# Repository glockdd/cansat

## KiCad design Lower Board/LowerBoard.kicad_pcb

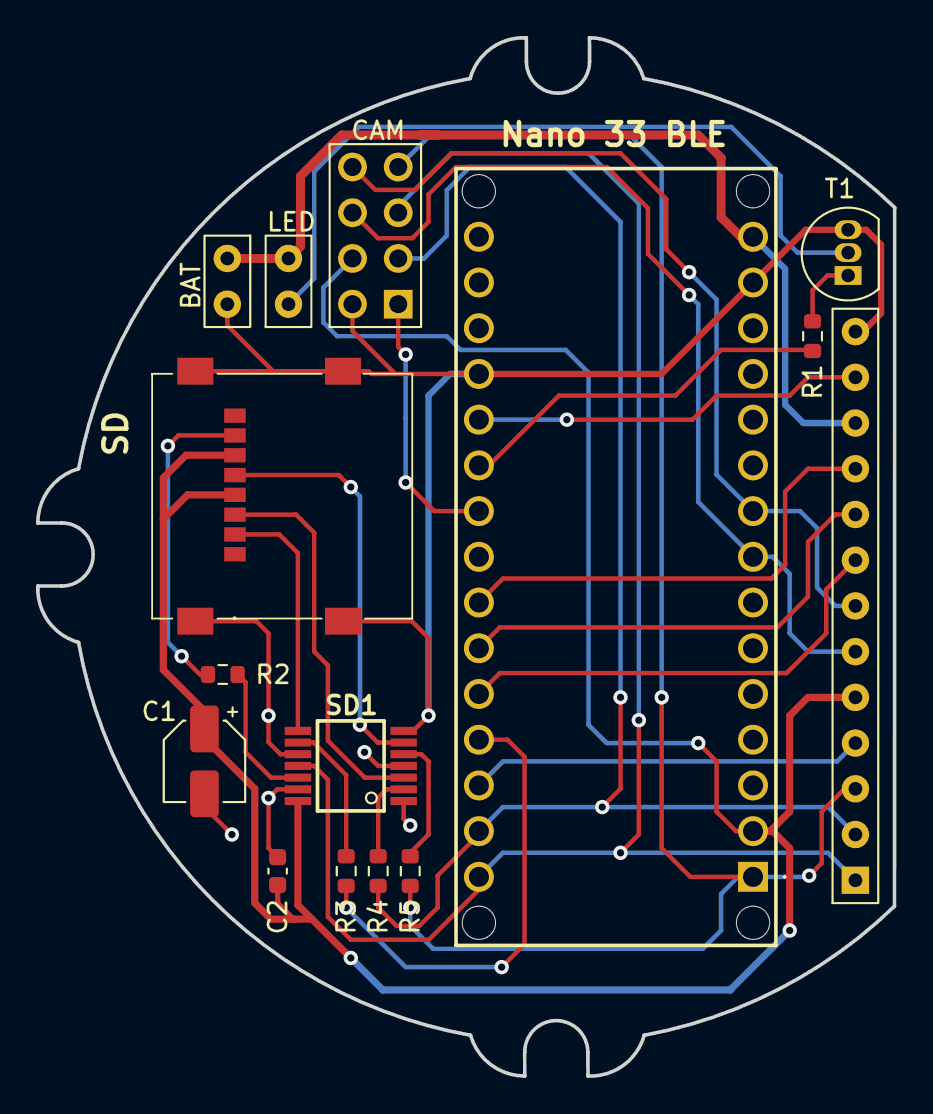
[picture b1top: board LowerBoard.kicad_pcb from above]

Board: 2 copper layers, 47.6 x 57.7 mm, 14 parts (0 on the bottom side), 21 nets.

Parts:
BAT: TP4056; Battery_Connector
C1: 4.7μF; CP_Elec_4x4.5
C2: 0.1μF; C_0603_1608Metric
CAM: OV5642
LED: LED Lights; Battery_Connector
Nano 33 BLE: Arduino Nano 33 BLE
R1: 6.8kΩ; R_0603_1608Metric
R2, R3, R4, R5: 3.3kΩ; R_0603_1608Metric
SD: MEM2067-02-180-00-A
SD1: 74LVC125APW
T1: TEMP (60-70); TO-92L_Inline

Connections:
+3.3V: C1.1, C2.1, CAM.6 (VCC), Nano 33 BLE.2 (+3V3), SD.P4 (VDD), SD.P6 (VSS), SD1.14 (VCC)
+5V: BAT.1 (IN+), LED.2 (A), Nano 33 BLE.15 (VIN)
CAM_CS: CAM.1 (CS), Nano 33 BLE.22 (D4)
CLK: CAM.4 (SCK), Nano 33 BLE.1 (D13), R5.2
CLK_SCK: SD.P5 (CLK), SD1.6 (2Y)
CS_CD: SD.P2 (CD/DAT3), SD1.8 (3Y)
Cam: LED.1 (K), T1.2 (C)
DI: SD.P3 (CMD), SD1.3 (1Y)
DO: R2.1, SD.P7 (DAT0)
GND: BAT.2 (IN-), C1.2, C2.2, CAM.5 (GND), Nano 33 BLE.14 (GND), Nano 33 BLE.19 (GND), SD.MP1, SD.MP2, SD.MP3, SD.MP4, SD1.1 (1~OE), SD1.4 (2~OE), SD1.7 (GND), SD1.10 (3~OE), SD1.13 (4~OE), T1.3 (E)
LED_Lights: Nano 33 BLE.21 (D3/PWM), R1.2
MISO: CAM.3 (MISO), Nano 33 BLE.30 (D12/MISO), SD1.11 (4Y)
MOSI: CAM.2 (MOSI), Nano 33 BLE.29 (D11/MOSI), R4.2
unnamed: R4.1, SD1.2 (1A)
unnamed: R5.1, SD1.5 (2A)
unnamed: R3.2, SD1.9 (3A)
unnamed: R2.2, SD1.12 (4A)
unnamed: R1.1, T1.1 (B)
SCL: CAM.8 (SCL), Nano 33 BLE.9 (A5/SCL)
SDA: CAM.7 (SDA), Nano 33 BLE.8 (A4/SDA)
SD_CS: Nano 33 BLE.27 (D9/PWM), R3.1

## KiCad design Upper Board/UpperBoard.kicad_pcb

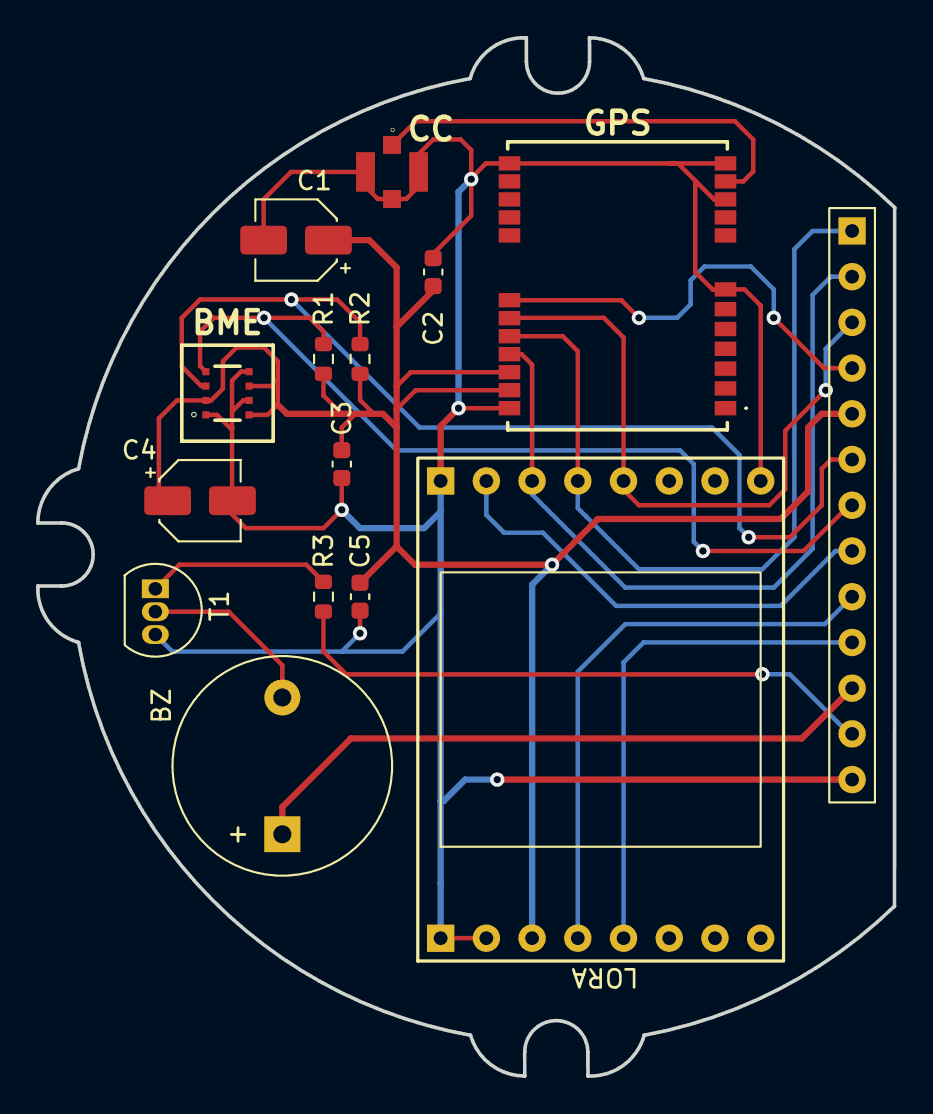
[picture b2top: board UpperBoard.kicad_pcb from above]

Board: 2 copper layers, 47.6 x 57.7 mm, 14 parts (0 on the bottom side), 10 nets.

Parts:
BME: BME688
BZ: Buzzer; Buzzer_12x9.5RM7.6
C1, C4: 4.7μF; CP_Elec_4x4.5
C2, C3, C5: 0.1μF; C_0603_1608Metric
CC: Coax_Connector; Coaxial_Connector
GPS: NEO-M8J
LORA: SX1728 LoRa; SX1728 LoRa Module
R1, R2: 4.7kΩ; R_0603_1608Metric
R3: 6.8kΩ; R_0603_1608Metric
T1: TEMP (60-70); TO-92L_Inline

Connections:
+3.3V: BME.2 (CSB), BME.6 (VDDIO), BME.8 (VDD), C1.1, C2.1, C3.1, C4.1, C5.1, GPS.22 (V_BCKP), GPS.23 (VCC), LORA.3 (3V3), R1.1, R2.1
CLK: GPS.19 (SCL_/_SPI_CLK), LORA.13 (SCK)
GND: BME.1 (GND), BME.5 (SDO), BME.7 (GND), C1.2, C2.2, C3.2, C4.2, C5.2, CC.2 (GND_1), CC.3 (GND_2), CC.4 (GND_3), GPS.7 (VDD_USB), GPS.10 (GND_1), GPS.12 (GND_2), GPS.13 (GND_3), GPS.24 (GND_4), LORA.1 (GND), LORA.2 (GND), LORA.9 (GND), LORA.16 (GND), T1.3 (E)
MISO: GPS.20 (TXD_/_SPI_MISO), LORA.12 (MISO)
MOSI: GPS.21 (RXD_/_SPI_MOSI), LORA.11 (MOSI)
unnamed: BZ.2 (+), T1.2 (C)
unnamed: CC.1 (SIGNAL), GPS.11 (RF_IN)
unnamed: R3.1, T1.1 (B)
SCL: BME.4 (SCK), R1.2
SDA: BME.3 (SDI), R2.2
